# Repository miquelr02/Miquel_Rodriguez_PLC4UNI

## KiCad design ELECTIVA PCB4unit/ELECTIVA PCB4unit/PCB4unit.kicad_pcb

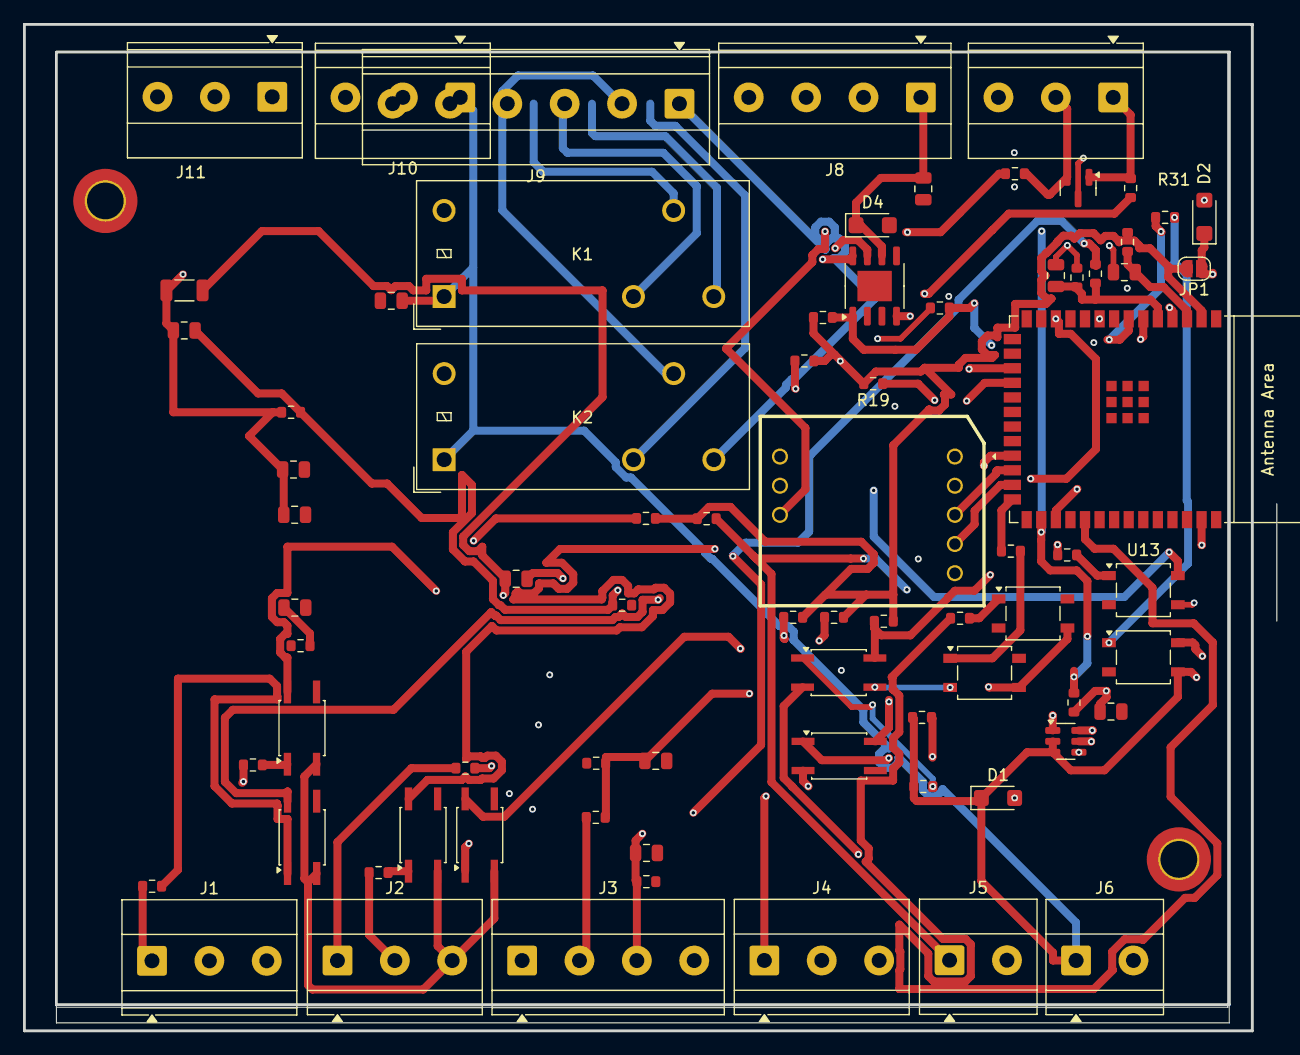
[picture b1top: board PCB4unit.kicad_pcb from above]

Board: 4 copper layers, 109.1 x 87.7 mm, 76 parts (0 on the bottom side), 61 nets.

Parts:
C1, C11: 1uF; C_0805_2012Metric
C2: 10uF; C_0805_2012Metric
C3, C7, C8, C9, C10, C12: 100nF; C_0805_2012Metric
C4: 100pF; C_0805_2012Metric
C5, C6: 22uF; C_0805_2012Metric
D1, D2, D4: SMF24A; D_SMF
D3: SM712_SOT23; SOT-23
J1, J2, J4, J7, J10, J11: Screw_Terminal_01x03; TerminalBlock_Phoenix_MKDS-1,5-3_1x03_P5.00mm_Horizontal
J3, J8: Screw_Terminal_01x04; TerminalBlock_Phoenix_MKDS-1,5-4_1x04_P5.00mm_Horizontal
J5, J6: Screw_Terminal_01x02; TerminalBlock_Phoenix_MKDS-1,5-2_1x02_P5.00mm_Horizontal
J9: Screw_Terminal_01x06; TerminalBlock_Phoenix_MKDS-1,5-6_1x06_P5.00mm_Horizontal
JP1: SolderJumper_2_Open; SolderJumper-2_P1.3mm_Open_RoundedPad1.0x1.5mm
K1, K2: G2RL-1; Relay_SPDT_Omron_G2RL-1
L1: 6.8uH; L_1206_3216Metric
R1, R4, R25: 10k; R_0603_1608Metric
R2, R3: 4.7k; R_0603_1608Metric
R5: 196k; R_0603_1608Metric
R6: 62k; R_0603_1608Metric
R7, R8, R13, R14: 120; R_0603_1608Metric
R9, R10, R17, R18, R26, R27: 910; R_0603_1608Metric
R11, R12, R19, R20, R28, R29: 412; R_0603_1608Metric
R15, R16, R30, R31: 100; R_0603_1608Metric
R21: 160k; R_0603_1608Metric
R22: 13k; R_0603_1608Metric
R23: 51k; R_0603_1608Metric
R24: 16k; R_0603_1608Metric
U1: ESP32-S3-WROOM-1
U2: AP63200WU; TSOT-23-6
U3: YLPTEC RSM3485ECHT
U4, U5, U8, U9, U11, U12: LTV-357TB; SO-4_4.4x3.6mm_P2.54mm
U6, U7, U13, U14: SO-4_4.4x4.3mm_P2.54mm
U10: eSOP-8

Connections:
+3.3V: JP1.2 (B), R1.1, R2.1, R3.1, R4.1, R11.2, R12.2, R19.2, R20.2, R28.2, R29.2, U1.2 (3V3), U3.1 (VCC)
/NIVARA_BOARD/+10V_AINPUT: J3.1, R23.1
/NIVARA_BOARD/+32V_AINPUT: J3.2, R21.1
/NIVARA_BOARD/DRY_DINPUT_0: J4.1, U8.2
/NIVARA_BOARD/DRY_DINPUT_1: J4.2, U9.2
/NIVARA_BOARD/Entradas_NPN/NPN_Output0: R11.1, U4.4
/NIVARA_BOARD/Entradas_NPN/NPN_Output1: R12.1, U5.4
/NIVARA_BOARD/NPN_DINPUT_0: J1.1, R9.1
/NIVARA_BOARD/NPN_DINPUT_1: J1.2, R10.1
/NIVARA_BOARD/NPN_DOUTPUT_0: J10.2, U6.3, U7.3
/NIVARA_BOARD/PNP_DINPUT_0: J2.1, R26.1
/NIVARA_BOARD/PNP_DINPUT_1: J2.2, R27.1
/NIVARA_BOARD/PNP_DOUTPUT_0: J11.2, U13.4
/NIVARA_BOARD/PNP_DOUTPUT_1: J11.3, U14.4
/NIVARA_BOARD/RL1_COM: J9.3, K2.11
/NIVARA_BOARD/RL1_OUTPUT_NC: J9.2, K2.12
/NIVARA_BOARD/RL1_OUTPUT_NO: J9.1, K2.14
/NIVARA_BOARD/RL2_COM: J9.6, K1.11
/NIVARA_BOARD/RL2_OUTPUT_NC: J9.5, K1.12
/NIVARA_BOARD/RL2_OUTPUT_NO: J9.4, K1.14
/NIVARA_BOARD/RS485_A: D3.1 (A1), J7.1, R8.2
/NIVARA_BOARD/RS485_B: D3.2 (A2), J7.2, R7.2
/NIVARA_BOARD/Salida_mA/mA_IN: C7.1, R13.2
/NIVARA_BOARD/VOLTAGE_AOUTPUT: C12.2, D4.1 (A1), J8.1, U10.6 (VOUT)
/NIVARA_BOARD/~RUN/STOP: J5.1, R1.2, U1.29 (SPIIO7/GPIO36/FSPICLK/SUBSPICLK)
GND: C1.2, C2.1, C5.1, C6.1, C7.2, C8.2, C9.2, C10.2, C11.1, C12.1, D1.2 (A2), D2.2 (A2), D3.3 (common), D4.2 (A2), J3.4, J4.3, J5.2, J6.2, J7.3, J8.4, J11.1, R6.2, R13.1, R14.1, R22.2, R24.2, U1.1 (GND), U1.40 (GND), U1.41 (GND), U2.4 (GND), U3.2 (GND), U4.3, U5.3, U6.2, U6.4, U7.2, U7.4, U8.3, U9.3, U10.5 (GND), U11.3, U12.3, U13.2, U14.2
GPIO1: C8.1, J3.3, R14.2, U1.39 (GPIO1/TOUCH1/ADC1_CH0)
GPIO4: C9.1, R21.2, R22.1, U1.4 (GPIO4/TOUCH4/ADC1_CH3)
GPIO5: C10.1, R23.2, R24.1, U1.5 (GPIO5/TOUCH5/ADC1_CH4)
GPIO6: R30.1, U1.6 (GPIO6/TOUCH6/ADC1_CH5)
GPIO7: R31.1, U1.7 (GPIO7/TOUCH7/ADC1_CH6)
GPIO8: R28.1, U1.12 (GPIO8/TOUCH8/ADC1_CH7/SUBSPICS1), U11.4
GPIO9: R29.1, U1.17 (GPIO9/TOUCH9/ADC1_CH8/FSPIHD/SUBSPIHD), U12.4
GPIO10: R19.1, U1.18 (GPIO10/TOUCH10/ADC1_CH9/FSPICS0/FSPIIO4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), U8.4
GPIO16: R2.2, R3.2, U1.9 (GPIO16/U0CTS/ADC2_CH5/XTAL_32K_N), U10.1 (SCLK)
GPIO21: R20.1, U1.23 (GPIO21), U9.4
GPIO38: R15.1, U1.31 (GPIO38/FSPIWP/SUBSPIWP)
GPIO45: R16.1, U1.26 (GPIO45)
GPIO47: U1.24 (GPIO47/SPICLK_P/SUBSPICLK_P_DIFF), U3.3 (TXD)
GPIO48: U1.25 (GPIO48/SPICLK_N/SUBSPICLK_N_DIFF), U3.4 (RXD)
unnamed: C4.1, C5.2, C6.2, D2.1 (A1), JP1.1 (A), L1.2, R5.1
unnamed: R9.2, U4.1
unnamed: R10.2, U5.1
unnamed: R15.2, U6.1
unnamed: R16.2, U7.1
unnamed: R17.2, U8.1
unnamed: R18.2, U9.1
unnamed: R26.2, U11.1
unnamed: R27.2, U12.1
unnamed: R30.2, U13.1
unnamed: R31.2, U14.1
unnamed: C1.1, R4.2, U1.3 (EN)
unnamed: C3.1, U2.6 (BST)
unnamed: C4.2, R5.2, R6.1, U2.1 (FB)
unnamed: C3.2, L1.1, U2.5 (SW)
unnamed: R8.1, U3.9 (A)
unnamed: R7.1, U3.8 (B)
unnamed: C11.2, R25.2, U10.8 (V5V)
PNPIN_GND: J2.3, U4.2, U5.2, U11.2, U12.2
SPII06: R25.1, U1.28 (SPIIO6/GPIO35/FSPID/SUBSPID), U10.7 (SEL)
VCC: C2.2, D1.1 (A1), J6.1, J10.1, K1.A1, K2.A1, R17.1, R18.1, U2.2 (EN), U2.3 (IN), U10.4 (VCC), U13.3, U14.3

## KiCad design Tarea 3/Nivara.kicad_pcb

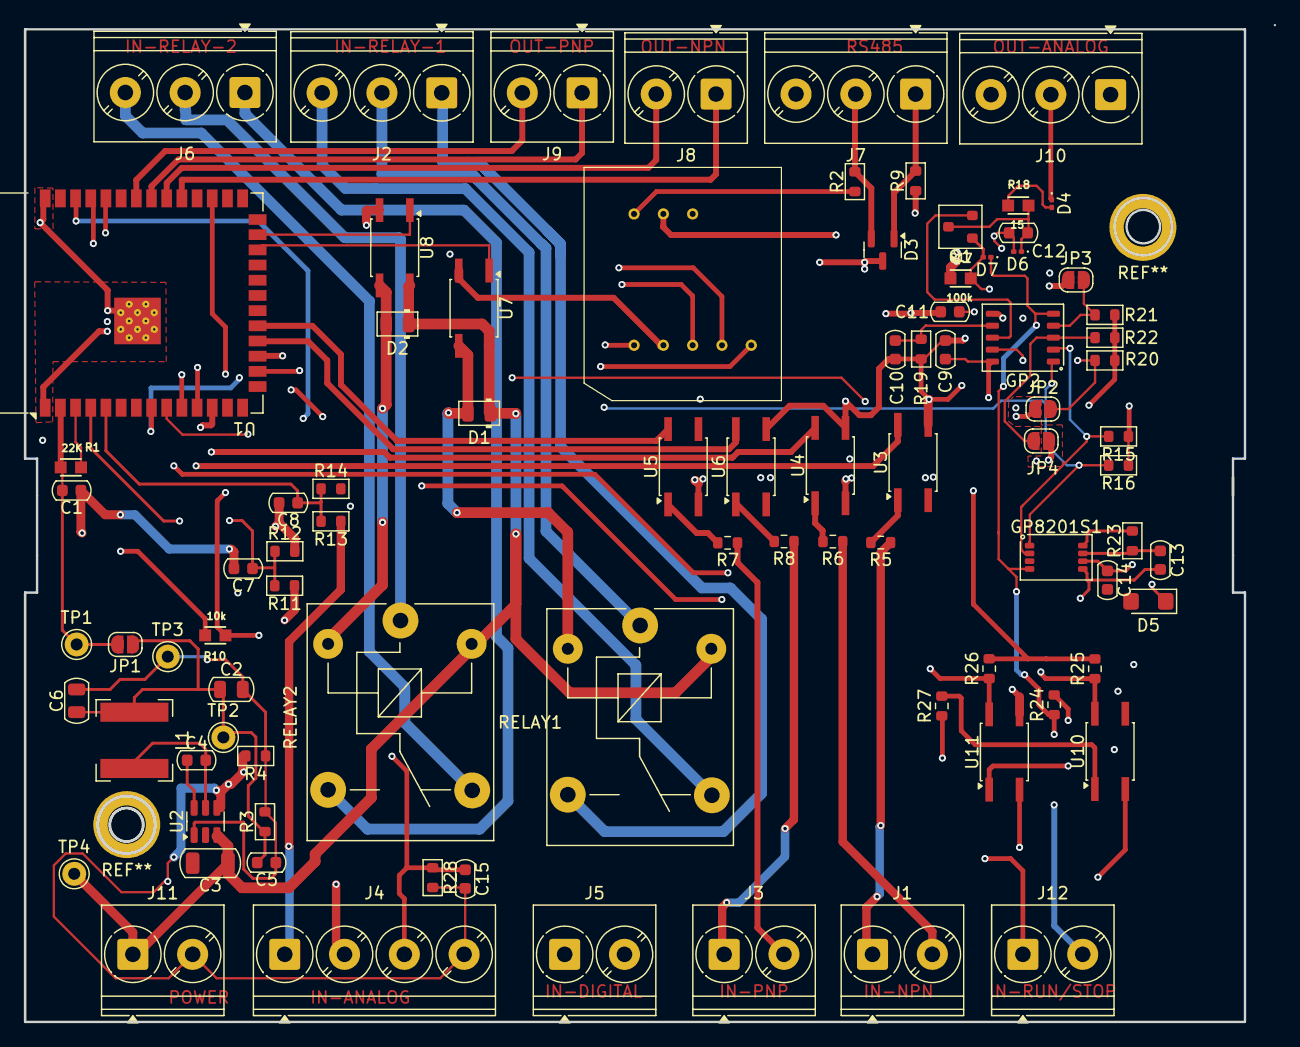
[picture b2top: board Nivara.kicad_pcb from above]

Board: 4 copper layers, 104.5 x 83.3 mm, 87 parts (0 on the bottom side), 68 nets.

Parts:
C1, C9, C11, C13: 1uF; C_0603_1608Metric
C2, C6: 22uF; C_0805_2012Metric
C3: 10uF; C_1206_3216Metric
C4, C7, C8, C14, C15: 100nF; C_0603_1608Metric
C5: 100PF; C_0603_1608Metric
C10: 220pF; C_0603_1608Metric
C12: 0.1uF; C_0603_1608Metric
D1, D2: CD4148WS; D_0805_2012Metric
D3: SM712_SOT23; SOT-23
D4: 1N4007; D_0201_0603Metric
D5: SMF24A; D_SMF
D6, D7: SMF24A; D_0201_0603Metric
GP2: SSOP-10_3.9x4.9mm_P1.00mm
GP8201S1: OnSemi_Micro8
J1: IN-NPN; TerminalBlock_Phoenix_PT-1,5-2-5.0-H_1x02_P5.00mm_Horizontal
J2: IN-RELAY-1; TerminalBlock_Phoenix_PT-1,5-3-5.0-H_1x03_P5.00mm_Horizontal
J3: IN-PNP; TerminalBlock_Phoenix_PT-1,5-2-5.0-H_1x02_P5.00mm_Horizontal
J4: IN-ANALOG; TerminalBlock_Phoenix_PT-1,5-4-5.0-H_1x04_P5.00mm_Horizontal
J5: IN-DIGITAL; TerminalBlock_Phoenix_PT-1,5-2-5.0-H_1x02_P5.00mm_Horizontal
J6: IN-RELAY-2; TerminalBlock_Phoenix_PT-1,5-3-5.0-H_1x03_P5.00mm_Horizontal
J7: RS485; TerminalBlock_Phoenix_PT-1,5-3-5.0-H_1x03_P5.00mm_Horizontal
J8: OUT-NPN; TerminalBlock_Phoenix_PT-1,5-2-5.0-H_1x02_P5.00mm_Horizontal
J9: OUT-PNP; TerminalBlock_Phoenix_PT-1,5-2-5.0-H_1x02_P5.00mm_Horizontal
J10: OUT-ANALOG; TerminalBlock_Phoenix_PT-1,5-3-5.0-H_1x03_P5.00mm_Horizontal
J11: POWER; TerminalBlock_Phoenix_PT-1,5-2-5.0-H_1x02_P5.00mm_Horizontal
J12: IN-RUN/STOP; TerminalBlock_Phoenix_PT-1,5-2-5.0-H_1x02_P5.00mm_Horizontal
JP1, JP2, JP3, JP4: SolderJumper_2_Open; SolderJumper-2_P1.3mm_Open_RoundedPad1.0x1.5mm
L1: 6.8uH; L_Bourns-SRN6028
Q1: AO3401A; SOT-23
R1: 22K; R_0603
R2, R9, R28: 120; R_0603_1608Metric
R3, R4: 22k; R_0603_1608Metric
R5, R6, R7, R8, R24, R27: 910; R_0603_1608Metric
R10: 10k; R_0603
R11, R13: 51k; R_0603_1608Metric
R12, R14: 16k; R_0603_1608Metric
R15, R16: 4.7k; R_0603_1608Metric
R17: 100k; R_0603
R18: 15; R_0603
R19: 2.5k; R_0603_1608Metric
R20, R21, R22, R23: 10k; R_0603_1608Metric
R25, R26: 412; R_0603_1608Metric
RELAY1, RELAY2: SANYOU_SRD_Form_C; Relay_SPDT_SANYOU_SRD_Series_Form_C
TP1, TP2, TP3, TP4: TestPoint; Pin_D1.0mm_L10.0mm
U1: ESP32-S3-WROOM-1
U2: AP63200WU; TSOT-23-6
U3, U4, U5, U6, U7, U8, U10, U11: LTV-357TB; SO-4_4.4x3.6mm_P2.54mm
U9: RSM3485ECHT

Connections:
+3.3V: C1.2, JP1.2 (B), R1.1, R10.1, R15.1, R16.1, R25.2, R26.2, TP1.1, U1.2 (3V3), U9.1 (VCC)
/BOARD/ANAG_0-10-IN: J4.2, R11.1
/BOARD/ANAG_0-32-IN: J4.1, R13.1
/BOARD/ANAG_VOL-OUT: C14.1, D5.1 (A1), GP8201S1.6 (VOUT)
/BOARD/DIG_IN/OUT_DIGITAL_0: R25.1, U1.10 (IO17), U10.4
/BOARD/DIG_IN/OUT_DIGITAL_1: R26.1, U1.11 (IO18), U11.4
/BOARD/IN-PNP1: J3.1, R8.1
/BOARD/IN-PNP2: J3.2, R7.1
/BOARD/INPUT_NPN/OUTPUT_NPN1: U1.12 (IO8), U3.4
/BOARD/INPUT_NPN/OUTPUT_NPN2: U1.17 (IO9), U4.4
/BOARD/INPUT_PNP/OUTPUT-PNP1: U1.18 (IO10), U6.4
/BOARD/INPUT_PNP/OUTPUT-PNP2: U1.19 (IO11), U5.4
/BOARD/IN_DIGITAL_0: J5.2, U10.2
/BOARD/IN_DIGITAL_1: J5.1, U11.2
/BOARD/IN_NPN1: J1.1, R5.1
/BOARD/IN_NPN2: J1.2, R6.1
/BOARD/IN_mA-ANAG: C15.1, J4.3, R28.1, U1.38 (IO2)
/BOARD/OUTPUT-PNP1: J9.1, U1.33 (IO40)
/BOARD/OUTPUT-PNP2: J9.2, U1.34 (IO41)
/BOARD/OUTPUT_NPN1: J8.1, U1.31 (IO38)
/BOARD/OUTPUT_NPN2: J8.2, U1.32 (IO39)
/BOARD/OUT_4-20mA-ANAG: D4.1 (K), J10.2
/BOARD/RELA2_NO: J6.1, RELAY2.3
/BOARD/RELAY1_COS: J2.2, RELAY1.1
/BOARD/RELAY1_NC: J2.3, RELAY1.4
/BOARD/RELAY1_NO: J2.1, RELAY1.3
/BOARD/RELAY2_COS: J6.2, RELAY2.1
/BOARD/RELAY2_NC: J6.3, RELAY2.4
/BOARD/RELAY-SETUP/ACT_RELAY1: U1.24 (IO47), U7.1
/BOARD/RELAY-SETUP/ACT_RELAY2: U1.25 (IO48), U8.1
/BOARD/RS485-DRIVER/UART-IN: U1.37 (TXD0), U9.3 (TXD)
/BOARD/RS485-DRIVER/UART-OUT: U1.36 (RXD0), U9.4 (RXD)
/BOARD/RS485-DRIVER/~TX/RX: U1.16 (IO46), U9.5 (CON)
/BOARD/RS-485A: D3.1 (A1), J7.1, R9.2
/BOARD/RS-485B: D3.2 (A2), J7.2, R2.2
/BOARD/VOLTAGE entrada/ANAG_0-10-OUT: C7.1, R11.2, R12.1, U1.4 (IO4)
/BOARD/VOLTAGE entrada/ANAG_0-32-OUT: C8.1, R13.2, R14.1, U1.5 (IO5)
/BOARD/salida mA/SCLK_OUT: GP2.1 (SCLK), GP8201S1.1 (SCLK), R16.2, U1.9 (IO16)
/BOARD/salida mA/SDA_OUT: GP2.2 (SDA), GP8201S1.2 (SDA), R15.2, U1.8 (IO15)
/BOARD/~RUN/STOP: J12.1, R10.2, U1.29 (IO36)
GND: C1.1, C3.2, C7.2, C8.2, C9.2, C10.2, C11.2, C12.2, C13.2, C14.2, C15.2, D3.3 (common), D5.2 (A2), D6.2 (A2), GP2.6 (GND), GP8201S1.5 (GND), J4.4, J7.3, J10.3, J11.2, J12.2, JP2.1 (A), JP3.1 (A), JP4.1 (A), R4.2, R12.2, R14.2, R17.2, R19.2, R28.2, U1.1 (GND), U1.40 (GND), U1.41 (GND), U2.4 (GND), U3.2, U3.3, U4.2, U4.3, U5.2, U5.3, U6.2, U6.3, U7.2, U8.2, U9.2 (GND), U10.3, U11.3
unnamed: D1.2 (A), RELAY1.2, U7.3
unnamed: D2.2 (A), RELAY2.2, U8.3
unnamed: D4.2 (A), R18.2
unnamed: C12.1, D6.1 (A1), Q1.3 (D), R18.1
unnamed: C11.1, D7.2 (A2), Q1.1 (G), R17.1
unnamed: GP2.3 (A0), JP4.2 (B), R22.2
unnamed: GP2.4 (A1), JP3.2 (B), R21.2
unnamed: GP2.9 (A2), JP2.2 (B), R20.2
unnamed: C10.1, GP2.7 (SET), R19.1
unnamed: C9.1, GP2.10 (V5V), R20.1, R21.1, R22.1
unnamed: C13.1, GP8201S1.7 (SEL), R23.1
unnamed: GP8201S1.8 (V5V), R23.2
unnamed: C2.1, C5.2, C6.1, JP1.1 (A), L1.2, R3.1, TP2.1
unnamed: R5.2, U3.1
unnamed: R6.2, U4.1
unnamed: R7.2, U5.1
unnamed: R8.2, U6.1
unnamed: R24.2, U11.1
unnamed: R27.2, U10.1
unnamed: R1.2, U1.3 (EN)
unnamed: C4.1, U2.6 (BST)
unnamed: C2.2, C5.1, C6.2, R3.2, R4.1, TP3.1, U2.1 (FB)
unnamed: C4.2, L1.1, U2.5 (SW)
unnamed: R9.1, U9.9 (A)
unnamed: R2.1, U9.8 (B)
VCC: C3.1, D1.1 (K), D2.1 (K), D7.1 (A1), GP2.5 (VCC), GP8201S1.4 (VCC), J11.1, R24.1, R27.1, RELAY1.5, RELAY2.5, TP4.1, U2.2 (EN), U2.3 (IN), U7.4, U8.4
i_out: GP2.8 (IOUT), Q1.2 (S)
